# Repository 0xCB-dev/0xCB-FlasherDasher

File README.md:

# ISP Flasher

## High Speed ISP flasher using the SPI of a Raspberry Pi

### Used Hardware

- Raspberry Pi3b+ (any pi with the new header layout and SPI will do)
- this [case](https://www.prusaprinters.org/prints/15876-raspberry-pi-3-sleeve-case/files)
- Sparkfun Raspberry Pi Shield: [DEV-14747](https://www.sparkfun.com/products/14747)
- ISP adapters in this repo

### Setup

- install OS to SD or USB: I used [DietPI](https://dietpi.com/) but you can use anything you like.
- Enable SPI: `nano /boot/config.txt` add / edit `dtparam=spi=on` and `reboot`
- install avrdude with SPI enabled following this [guide](http://kevincuzner.com/2013/05/27/raspberry-pi-as-an-avr-programmer/)
- install pigs `apt update && apt-get install pigpio` enable `sudo systemctl enable --now pigpiod`
- install git for git grep `apt install git`
- place flash.sh in /root/ and `chmod +x /root/flash.sh`
- add service `nano /etc/systemd/system/flasherdasher.service` and paste in the content of flasherdasher.service in this repo. `systemctl enable --now flasherdasher`
- format a USB stick in FAT32 and get the UUID with `blkid` 
- place the config on the USB stick and edit the UUID 
- add your hex to the USB and edit the fuse bits, firmware name, lock bit and flashing speeds to your liking

## Happy flashing!

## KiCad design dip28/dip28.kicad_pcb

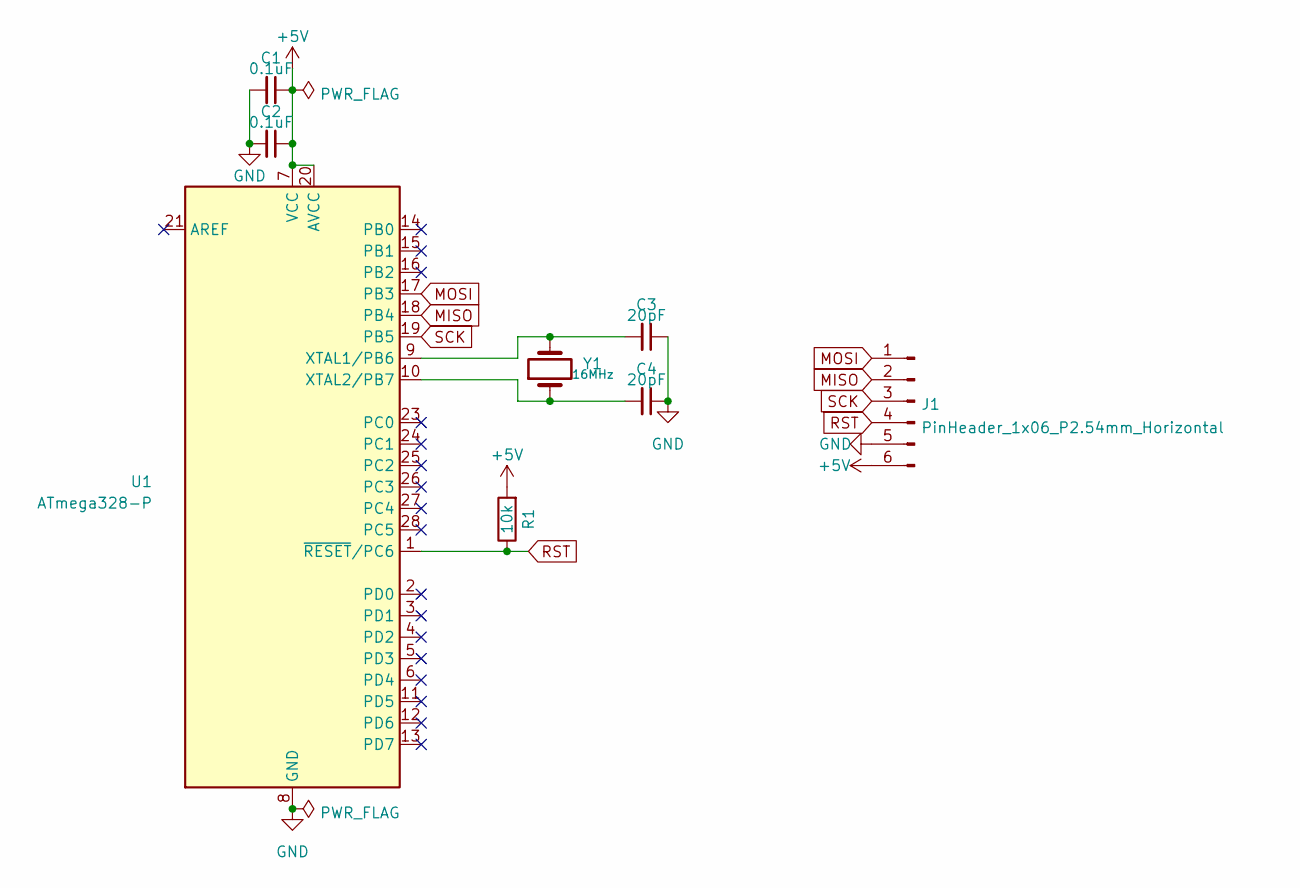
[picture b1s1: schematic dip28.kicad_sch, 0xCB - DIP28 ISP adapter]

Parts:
C1, C2: 0.1uF; C_Disc_D5.0mm_W2.5mm_P5.00mm; Part Nb. C277965
C3, C4: 20pF; C_Disc_D3.0mm_W1.6mm_P2.50mm; Part Nb. C254096
J1: PinHeader_1x06_P2.54mm_Horizontal
R1: 10k; R_Axial_DIN0204_L3.6mm_D1.6mm_P5.08mm_Horizontal; Part Nb. C58673
U1: ATmega328-P; Part Nb. C613508
Y1: 16MHz; Crystal_HC49-4H_Vertical; Part Nb. C16212

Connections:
+5V: C1.1, C2.1, J1.6, R1.2, U1.7 (VCC), U1.20 (AVCC)
GND: C1.2, C2.2, C3.1, C4.1, J1.5, U1.8 (GND), U1.22 (GND)
MISO: J1.2, U1.18 (PB4)
MOSI: J1.1, U1.17 (PB3)
unnamed: C3.2, U1.9 (XTAL1/PB6), Y1.2
unnamed: C4.2, U1.10 (XTAL2/PB7), Y1.1
RST: J1.4, R1.1, U1.1 (~RESET/PC6)
SCK: J1.3, U1.19 (PB5)

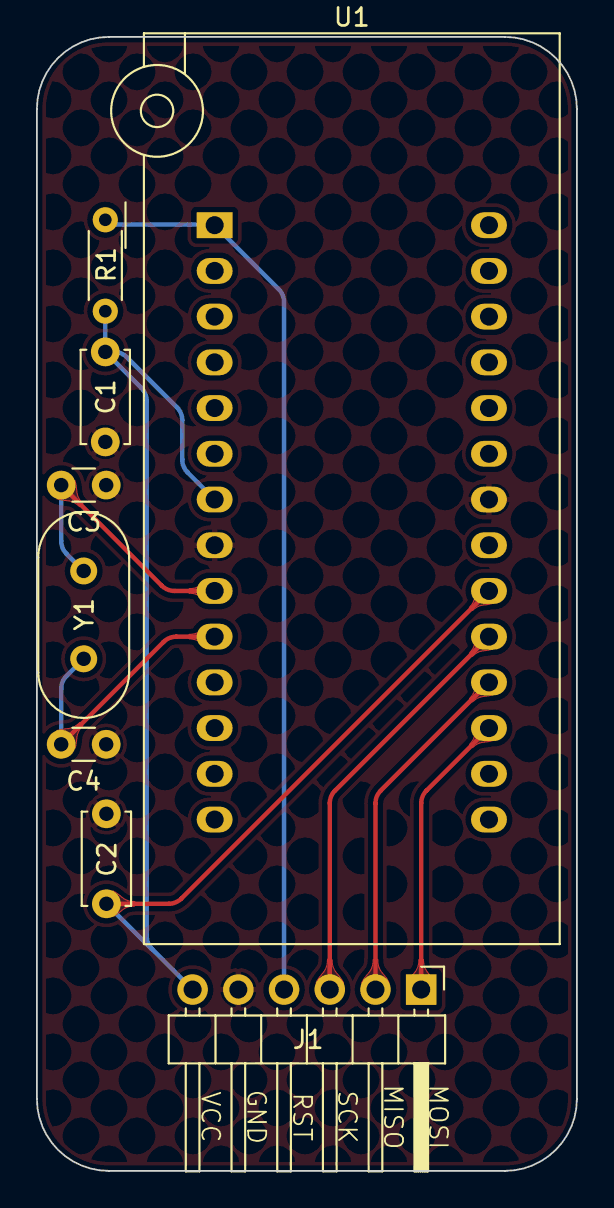
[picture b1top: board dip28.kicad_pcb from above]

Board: 2 copper layers, 30.0 x 63.0 mm, 8 parts (0 on the bottom side), 8 nets.

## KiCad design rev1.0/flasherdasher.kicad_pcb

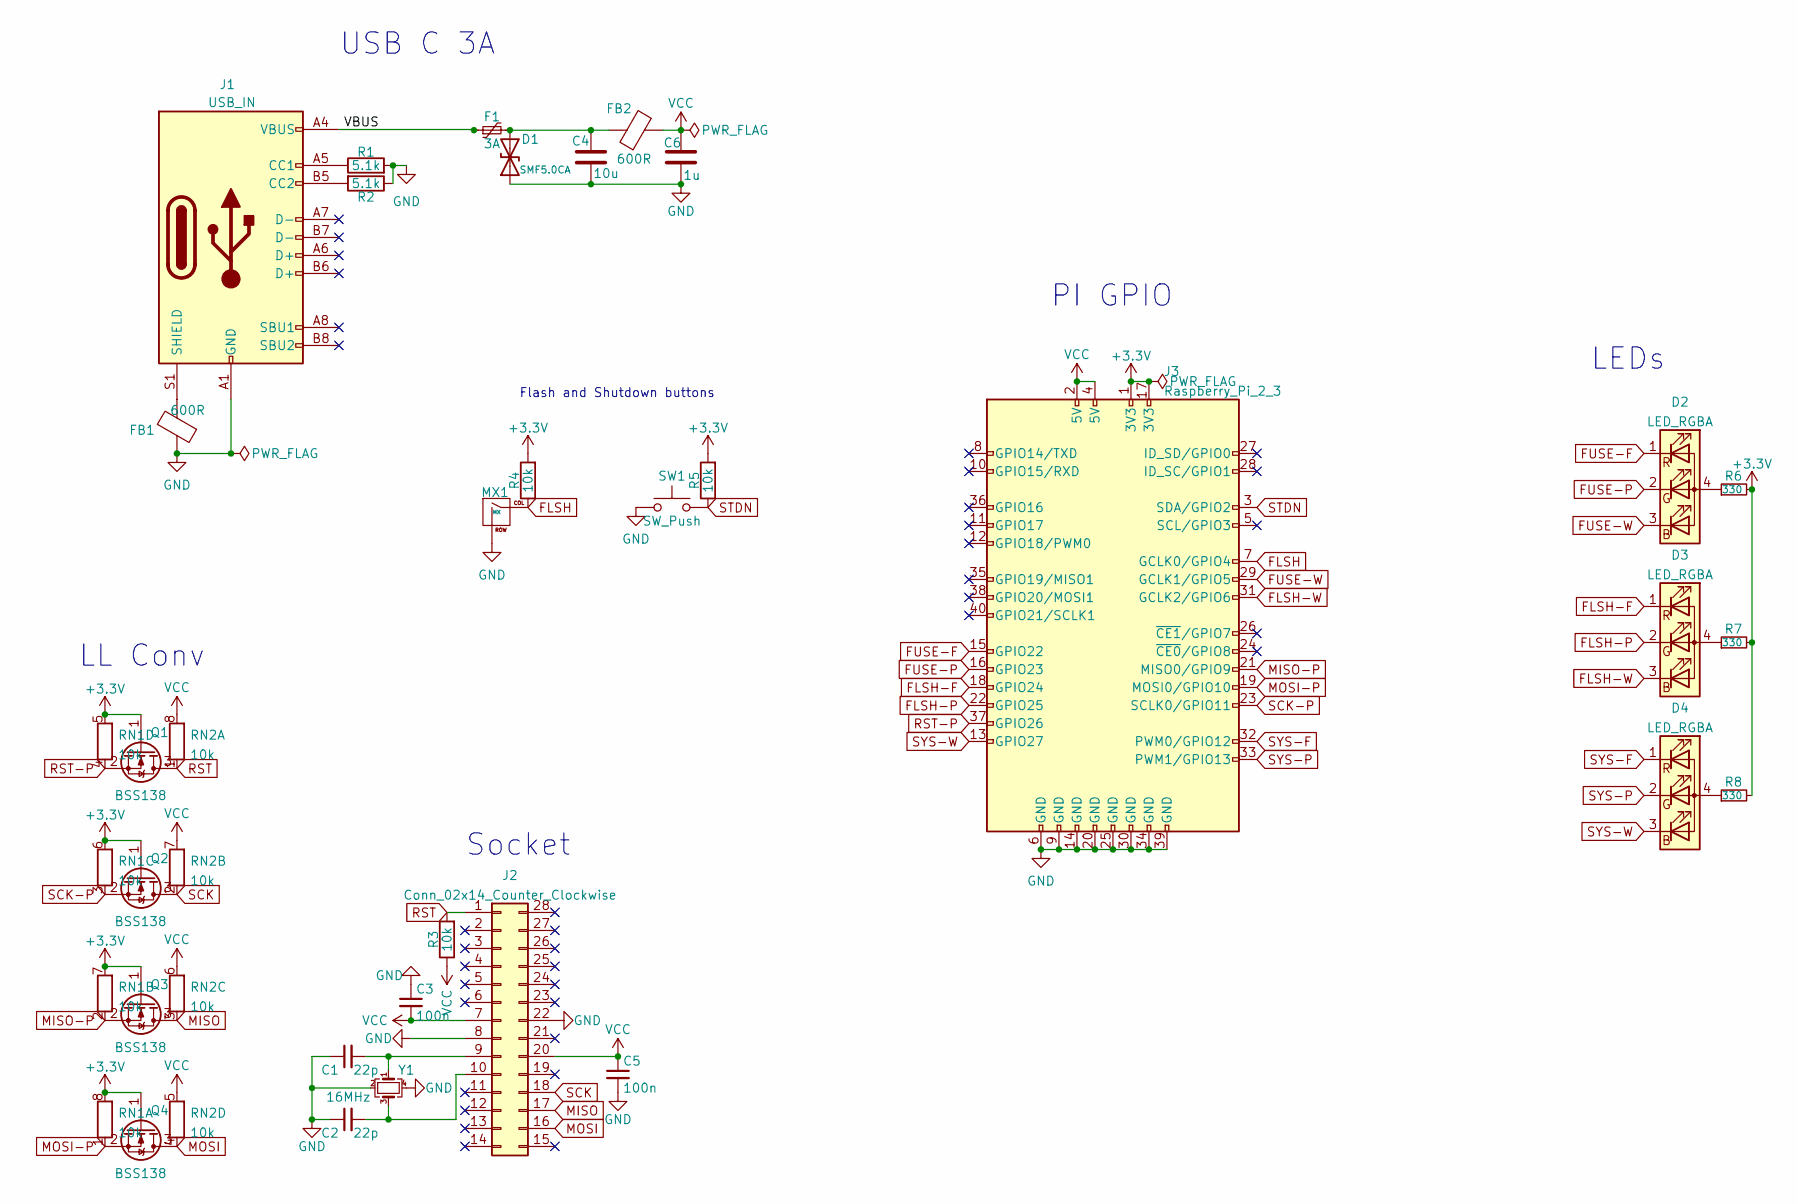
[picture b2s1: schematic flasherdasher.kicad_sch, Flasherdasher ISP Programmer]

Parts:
C1, C2: 22p; C_0603_1608Metric; Part Nb. 478-1167-1-ND
C3, C5: 100n; C_0603_1608Metric; Part Nb. 478-5266-1-ND
C4: 10u; C_0603_1608Metric
C6: 1u; C_0603_1608Metric
D1: SMF5.0CA; D_SOD-123F
D2, D3, D4: LED_RGBA; LED_EAST1616RGBA3
F1: 3A; Fuse_0805_2012Metric; Part Nb. 507-1815-1-ND
FB1, FB2: 600R; Ferrite_Bead_0603
J1: USB_IN; molex2169900001; Part Nb. 900-2169900002CT-ND
J2: Conn_02x14_Counter_Clockwise; DIP_Socket-28_W6.9_W7.62_W10.16_W12.7_W13.5_3M_228-4817-00-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
J3: Raspberry_Pi_2_3; PinSocket_2x20_P2.54mm_Vertical
MX1: MX; SW_Cherry_MX_PCB_1.00u
Q1, Q2, Q3, Q4: BSS138; SOT-23
R1, R2: 5.1k; R_0603_1608Metric; Part Nb. P5.1KDBCT-ND
R3, R4, R5: 10k; R_0603_1608Metric; Part Nb. P5.1KDBCT-ND
R6, R7, R8: 330; R_1206_3216Metric; Part Nb. A130532CT-ND
RN1, RN2: 10k; R_Array_Convex_4x0603
SW1: SW_Push; SW_SPST_TL3342; Part Nb. EG2531CT-ND
Y1: 16MHz; Crystal_SMD_3225-4Pin_3.2x2.5mm; Part Nb. XC2060CT-ND

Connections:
+3V3: J3.1 (3V3), J3.17 (3V3), Q1.1 (G), Q2.1 (G), Q3.1 (G), Q4.1 (G), R4.2, R5.2, R6.2, R7.2, R8.2, RN1.5 (R4.2), RN1.6 (R3.2), RN1.7 (R2.2), RN1.8 (R1.2)
/VBUS: F1.1, J1.A4 (VBUS), J1.A9 (VBUS), J1.B4 (VBUS), J1.B9 (VBUS)
FLSH: J3.7 (GCLK0/GPIO4), MX1.1 (COL), R4.1
FLSH-F: D3.1 (RK), J3.18 (GPIO24)
FLSH-P: D3.2 (GK), J3.22 (GPIO25)
FLSH-W: D3.3 (BK), J3.31 (GCLK2/GPIO6)
FUSE-F: D2.1 (RK), J3.15 (GPIO22)
FUSE-P: D2.2 (GK), J3.16 (GPIO23)
FUSE-W: D2.3 (BK), J3.29 (GCLK1/GPIO5)
GND: C1.1, C2.1, C3.1, C4.2, C5.2, C6.2, D1.1 (A1), FB1.1, J1.A1 (GND), J1.A12 (GND), J1.B1 (GND), J1.B12 (GND), J2.8, J2.22, J3.6 (GND), J3.9 (GND), J3.14 (GND), J3.20 (GND), J3.25 (GND), J3.30 (GND), J3.34 (GND), J3.39 (GND), MX1.2 (ROW), R1.2, R2.1, SW1.1, Y1.2, Y1.4
MISO: J2.17, Q3.3 (D), RN2.3 (R3.1)
MISO-P: J3.21 (MISO0/GPIO9), Q3.2 (S), RN1.2 (R2.1)
MOSI: J2.16, Q4.3 (D), RN2.4 (R4.1)
MOSI-P: J3.19 (MOSI0/GPIO10), Q4.2 (S), RN1.1 (R1.1)
unnamed: C2.2, J2.10, Y1.3
unnamed: C4.1, D1.2 (A2), F1.2, FB2.1
unnamed: D2.4 (A), R6.1
unnamed: D3.4 (A), R7.1
unnamed: D4.4 (A), R8.1
unnamed: J1.A5 (CC1), R1.1
unnamed: J1.B5 (CC2), R2.2
unnamed: FB1.2, J1.S1 (SHIELD)
unnamed: C1.2, J2.9, Y1.1
RST: J2.1, Q1.3 (D), R3.2, RN2.1 (R1.1)
RST-P: J3.37 (GPIO26), Q1.2 (S), RN1.4 (R4.1)
SCK: J2.18, Q2.3 (D), RN2.2 (R2.1)
SCK-P: J3.23 (SCLK0/GPIO11), Q2.2 (S), RN1.3 (R3.1)
STDN: J3.3 (SDA/GPIO2), R5.1, SW1.2
SYS-F: D4.1 (RK), J3.32 (PWM0/GPIO12)
SYS-P: D4.2 (GK), J3.33 (PWM1/GPIO13)
SYS-W: D4.3 (BK), J3.13 (GPIO27)
VCC: C3.2, C5.1, C6.1, FB2.2, J2.7, J2.20, J3.2 (5V), J3.4 (5V), R3.1, RN2.5 (R4.2), RN2.6 (R3.2), RN2.7 (R2.2), RN2.8 (R1.2)

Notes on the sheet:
Socket
PI GPIO
Flash and Shutdown buttons
LL Conv
LEDs
USB C 3A

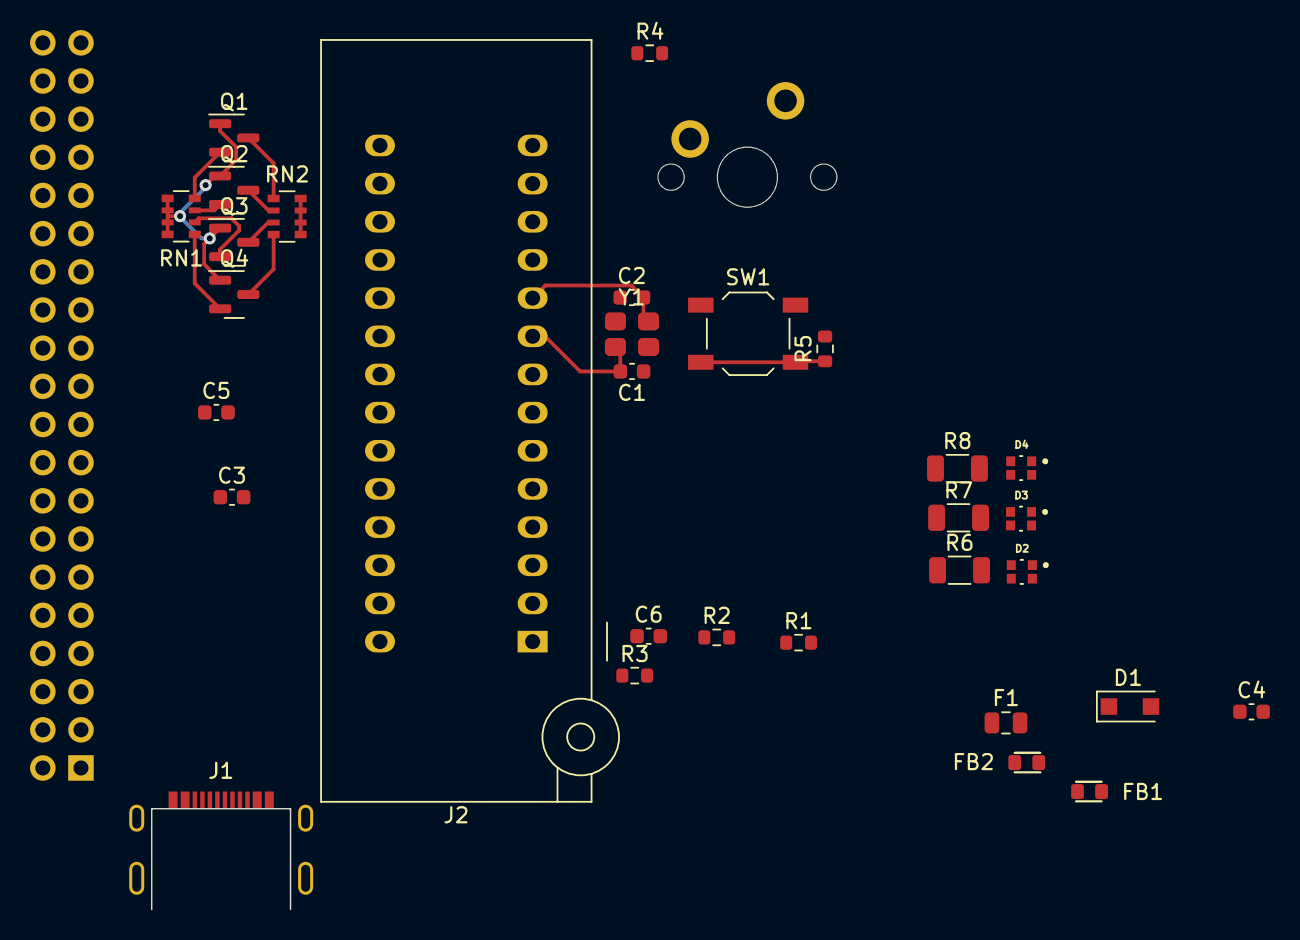
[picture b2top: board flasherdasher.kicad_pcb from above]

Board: 2 copper layers, 33 parts (1 on the bottom side), 32 nets.

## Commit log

2022-02-20 added script and hardware
2022-02-20 added missing deps
2022-05-04 fixed pogo and dip adapter
